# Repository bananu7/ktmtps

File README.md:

# Re-engineering a KTM Throttle Position Sensor

This a repository where I gathered and intend to update all the things related to the KTM 990 TPS. The sensor in those motorcycles is based on a potentiometer, and wears out quickly (head to [Original TPS](/reference/Original.md) for details). As such, I decided to try and create a hall-effect based replacement, as has become the industry standard.

## Work log

### 2024-01-26

It's right past midnight, so it should really be the note for Friday. I got the devkit-v2 casing printed. Quick notes

* needs a chamfer on the bottom where it enters the TBs
* needs more clearance around the pcb perimeter (not much though, likely just pcb has some unevenness)
* needs a bit less clearance for pcb centering tab (the bearing must fit there)
* the shaft needs more clearance inside the bearing (reduce shaft OD)
* bearing into casing clearance is OK
* the cablehole should be oval/wider and can be slightly lower

I'll try to tackle those tomorrow.

### 2024-01-25

The V2 devkits have arrived. Stock photo as they're everywhere:

I'm pleasantly surprised that i got the dimensions almost correctly from the photo. Here's how big the board is:

Since it's a circular shape, it's actually quite easy to design around it. I might just a centering lip to make sure the PCB doesn't rotate, otherwise it'll be held in place by an oring and and a cover.

I have to move the CAD files around, as i started to initially design for my own larger PCB, but the devkit v2 seems to actually be quite good and would save me a lot of time working, ordering and assembling them.

I'm still pondering on whether 2 bearings are even necessary. I might do one of the prototypes with just one bearing and see how it holds up.

### 2024-01-18

I've added early prototype files for CAD and PCB for v2. I think I found a decent way to mount the PCB, utilizing just the outline of the board
with no problematic alignment pins. I'll still need to find a way to do a board cutout to fix the angle, but the oring should keep it in place.
I will also add the screws to the cover and change the shape of the cable route.

I have ordered a couple of smaller devboards, so I might do a v2p CAD version that will accomodate those while i wait/finish my own PCBs.

### 2024-01-16

As almost three years pass from the last update, I decided to go back to the project. The prices of the OEM TPS keep rising, sitting at 160 eur currently. In addition, thanks to @gefr at advrider, we got a confirmation that the 990s ECU will happily work with the AS5600 unit. It's a newer, nicer rotation sensor based on the same principle. It can be trivially programmed via regular SPI without a need for a special programmer, and outputs the desired voltage range as analog PWM directly. So, what seems to remain is making a production-ready prototype.

There are two main challenges that need to be tackled - the PCB and the enclosure; with the latter mostly being dependent on the former. I've ordered a couple of smaller-size development boards from Aliexpress, but I think that eventually I'll need to make a new board. thankfully, the sensor requires absolutely minimum of external components, so the board can be made quite small. I am thinking about making it circular, with a notch for alignment, then covering it with an oring and screwing the cover over.

---

### 2021-09-19

Unfortunately, I got a bit stuck, and with the weather being nice, i just didn't make too much progress. I hope the coming winter months will give me a better time.

The biggest hurdle right now is fixing the dev board in. So far, while I was finally able to print the properly dimensioned pins (using the Cura's "modify mesh settings" to selectively slow down and increase infill for them), the dev board was just made so imprecisely that I couldn't get it to fit nicely. I just need to design my own board and order from JLC again, as that's proven to work way better. I can also include enough space for the mounting screw then.

As far as 3D printing goes, I did some research, and while Nylon (PA12) would be ideal for this application, basing on some tests I found online PLA is actually quite resistant to gasoline! I've mentioned that the ASA parts were disappointing, but I think I'm just going to go with PLA for the first truly functional prototype.

There is an additional thing worth mentioning. While searching the internet, I found a very similarly looking TPS unit, going around for around $20 - supposedly for Polaris vehicles. The physical dimensions look exactly the same, and some tests made on the forum seem to suggest that it might actually be electrically compatible. It has the wrong plug (the opposite sumimoto connector), but that's an easy fix. I've actually ordered one months ago, but Amazon has dropped the ball, so I'm waiting for a package from Aliexpress right now to do my own testing. I am not planning to abandon my project if it turns out to be a drop-in replacement, but it might be a good option for a lot of people.

---

### 2021-07-03

After over two months of waiting, I got a refund for the parts I've ordered and subsequently reordered them. They arrived a few days ago, and I was able to get back on track pretty quickly. This still required some nontrivial operations, though.

First off, in order to speed things up, I've ordered the sensors already soldered on a "development-kit" style of boards. They expose all the pins (7 on the board, because the chip has two Vcc pins, one for 3V3 and one for 5V) and come with convenient passive components. That "convenience" was actually quite problematic, because the way the chip is configured, it doesn't even produce an analog output at all! The R4 resistor puts it in a "programming" mode (the datasheet essentially allows it to be programmed by mechanical placement of the magnet and easy operations even without using I2C at all), so it had to be removed. Similarly, the R1 0Ohm resistor bridges the Vcc pins for 3V3 operation, and the chip works just fine at 5V after I got rid of it. I didn't have to reverse-engineer the board, so thanks to that one random Russian Aliexpress customer that put all of that information in his review.

The board has convenient 4mm mounting holes which I initially assumed to be spaced by 15mm. I took my ready CAD file, got rid of the perimeter plastic around the board (the new one wouldn't fit, anyway) and moved the pins around. That has proven to be an utter failure. Removing the wall around the pins meant that they had much less time to cool on every layer, so they came out as poorly defined blobs that broke out even before I got the print off the bed. No worries, though, as the board didn't fit anyway, with the holes apparently being spaced 16mm in one direction and **15.5mm** in the other. Eek. I just used wood screws to hold the board in place, for now. In fact, those sensors are so good that even holding the magnet in your fingers above the surface produces reasonable results! Compared to my earlier attempts with linear hall sensors, this is a huge difference.

As far as screws go, I was able to find a reasonable mounting screw for now, but I definitely need to redesign the PCB so that it's shorter on one end, because it does get annoying. Having more clearance near the screw would be really helpful.

That being said, after hooking up the direction pin to Vcc (this is a huge benefit of using the 5600 over the 5043!) for counter-clockwise-positive operation and putting it on the TB set, it worked just fine - albeit ratiometrically over 360 degrees. That was already great, though, as the chip can be straightforwardly programmed over just I2C with no HV required. In fact, instead of writing my own library, I used this [excellent example][11] with a human-friendly interface. Unfortunately during testing, even though I only wanted to play with runtime setting, I must've fat-fingered something and burned the angle settings in. Thankfully, the chip can accept that 3 times, so it wasn't bricked just yet.

> Note: The sensor has two possibilities of range settings that were (and still are) a bit confusing to me. Either you write into the MANG (angle) register to set the range of operation, or you write to ZPOS/MPOS to set the start and stop angles (corresponding to 0V and Vcc). Once the ZPOS/MPOS pair has been burned in, the MANG can't even be set dynamically. MANG can be burned in just once. ZPOS/MPOS can be burned in 3 times.

The software in the example works by allowing you to set the start and end values simply by rotating the magnet to appropriate position. Of course this is rather imprecise, but was enough for my testing. One more feature that it has is the raw angle display, which allowed me to more precisely measure the actual operating range of the sensor. To my surprise, it came out to only be **78 degrees**. I am not sure if the TBs have been zeroed-out prior to that, though, and will have to confirm with the original TPS. Either way, that meant that for testing I needed about 140 degrees of 0-5V sweep to get the desired mV/deg to obtain 0.6-3.8V.

This has worked beautifully. I rotated the sensor to indicate almost 0, programmed start position, turned it 140 degrees, programmed end position, and then burned the angle settings and unplugged the I2C connection. This is the first case of a successfully permanently programmed sensor that technically could go into the bike!

#### Wiring

This is also a good point to mention the wiring, as I've been working on that as well. The sensor needs to connect to the bike at the end!

For cables, I've ordered Polish-made TLWY brand ribbons, in 8x0.22mm^2, 8x0.35mm^2 and 8x0.5mm^2 (this corresponds to AWG 24, 22 and 20, respectively). They're of extremely high quality, meeting and exceeding automotive requirements. Even then, I am pretty sure that the original wiring uses AWG 18 cables, but for such a short connection I think I'm going to stick with 20.

The wire thickness is also important for the plug itself. Thanks to some research I found out that the original plugs used by KTM were originally manufactured by Sumimoto (**MT090**, 3-pin). KTM sells them, but they're about half as expensive when bought as generic automotive parts. I was very happy with my cost savings until I've realized that AliExpress has them for 1/5th the price again. Oh well, at least I'll be able to compare them.

To be quite honest, when they arrived, the only main difference seem to be the sealing rubbers. They're much firmer in the original ones, and a bit softer in the Chinese ones. I don't think this will have a huge effect. I mounted one plug so far using the TLWY wires with 1.7mm outer diameter and they seem to seal quite well. My crimping tool is technically only rated to AWG22, but it did just fine with those plugs. I'll wait until I have the casing for the dev-board prototype and will solder them on there.

I also bought a couple of the counterparts to potentially make some test setups. I think that I'll also make a usual Y-splitter to mount on the bike (just like the ones routinely used for TPS setting, even though you'd technically only need to branch that one voltage out).

#### Next steps

This was a long update written over a couple commits, but it represents a significant milestone for me. I've reached the point where I could conceivably take my sensor and plug it into a live bike, and thus its ECU, and see whether it likes the signal or not! I've realized that I don't even have to turn the engine on for that test, I can just ask TuneECU to tell me whether the computer sees the right input.

Before that happens, though, I need to create a proper casing just for the dev-board now and see how my plastic reacts to fuel vapors. I've been also thinking about putting some insulation sheet between the hole where the bearings sit and the electronics, as there need not be a direct contact there. The manual talks about an "airgap", but a thin mylar, kapton or similar sheet should work just fine.

After the unit is enclosed, has a proper screw and the plug connected, I'll consider it the first prototype ready for functional testing. There's a chance I might conduct just the electrical test first, but I see no reason why it shouldn't work with the ECU (since it presents an analog voltage just like a potentiometer would).

Of course even if the prototype works, there's still a question of a new PCB for the AS5600 (with more clearance), the spring loading (I've actually had a simpler idea that would clamp the shaft on the TB arm instead) et cetera, but there might be some things that only the functional testing of the prototype will reveal. I'd put it in my personal motorcycle if not for the fact that it needs to be ready for a long trip soon, so that'll have to wait until then.

---

### 2021-06-14

I've ordered the new sensor from Aliexpress, but the package hasn't arrived yet. In the meantime, I've built an enclosure for my 3D printer and successfully printed some ASA parts. Unfortunately, despite having excellent temperature and UV (we'll see about fuel vapors) resistance, they're much weaker mechanically, which was a disappointment.

---

### 2021-03-28

_This update has been copied from advrider forums._

I have some news - some bad, some good, but worth an update nonetheless.

The video from 2021-03-22 was showing the sensor programmed non-permanently. It had the configuration I needed, but once I resetted it (or cut power) it would go back to stock settings. The special programmer I tried to build was supposed to solve that and allow me to make the settings permanent.

I spent a week on it and got it to the point where I was pretty sure it was going to work, confirming the "correct" operation down to microseconds. Then I plugged the sensor in and... well, bricked it. It received some configuration, but decidedly not what I needed.

I still have a few units left, so I might try to fix the issues with this board, but meanwhile I've found yet another sensor (AS5600) that's:

- a newer design
- more accurate (12 vs 10 bits)
- much easier to program (no special programmer at all) - in fact, the rotation direction has a dedicated pin...
- much easier to solder (SOIC-8 vs SSOP-16)
- 6 times cheaper and easier to obtain
- also automotive-use qualified

I can only kick myself for not noticing it earlier. I think it should be a perfect replacement; I'm going to order some and try to work on the new plans. I wanted to make a V2 PCB anyway, to change the shape and make it easier to fit the mounting screw in the casing. The only downside is waiting for the PCBs to be made again, but after the first run I got more confident in being able to get them to work. I'll try ordering some pre-mounted boards with the new sensor as well to see if I can test it in practice even before my own PCBs are ready. Of course this means I'll need to alter the CAD designs too.

I could probably attack the programmer again and try to get it to work, but I think that at this point the time is better spent into preparing the new sensor; if only for the lower cost and much wider availability!

So while this is a bit of a hiccup, and my next iteration will take about a month to a month and a half to get all parts here, I think I've amassed enough experience to make it much closer to the final product.

In the meantime I might finally take a stab at setting up my 3D-printer for high-temperature materials to see if I'll be able to get a casing what would be usable in a real-world scenario.

---

### 2021-03-25

This is actually a summary of a few days of progress. I started working on the permanent OTP programmer for the AS sensor. I've designed a schematic and built it up on a prototype board from DIP parts. My initial idea was to utilize an ATtiny MCU programmed with the specific bit vector, but for the testing I just plugged the Uno into the DIP 8 socket.

This is the early version of the programmer board when I still thought I could get away with just two transistors. Since then I've severly modified the schematic to utilize a proper NPN driver and added caps across transistor base resistors to improve the shut-off time. The image below shows the delay that was caused by what's apparently called "Miller capacitance" or "charge storage", which I learned on [Electronics.se][10].

I also tried to generate pulses of exactly 2us; that turned out to be quite straighforward using the ATmega's Timer capabilities. The code showcasing that use is in `programmer/code/atmega328p_2u_pulse`.

An important realization I had was that the PROG timings aren't actually that crucial; it's the CLK timings that matter. At first I thought that I'll need to drive the HV line with that accuracy, but I can split the problem up. The PROG line needs to be driven consistently and with not too many transients (check) and the CLK line needs to generate exact 2us pulses (check). I think I have all parts of the puzzle now, what's left now is to integrate them together.

I've also just realized that since I connected the transistors to both PWM pins of the tiny pinout, I have none left for driving the CLK clock precisely. Uh. I'll need to figure something out.

---

### 2021-03-22 

I finally soldered a header to programming pins and took a stab at programming the sensors. So far, they seem to perform the best when the sensor is directly facing the magnet (and not through the PCB), which means the default rotation (value 0 for the MSB direction bit) is wrong.

The sensor can be programmed either permanently (via OTP) or just temporarily. The OTP programming starts with a regular "write" cycle, followed by high voltage pulses that permanently burn Zener diodes inside the chip to store the configuration. The serial interface for interacting with the unit is a bit different to the SSI used for digital readout (BTW, I've realized I skipped the digital data out (DO) on the PCB, which probably wasn't a great idea in retrospect). The SSI uses a very weird signal "delayed" by one clock pulse. The maximum frequency is specified as 1MHz. In contrary, programming allows up to 250kHz comparable to Mode 0 SPI, while the actual OTP burn requires very precisely timed pulses.

My first attempts ended with the chip not responding to anything I was sending so far. All the timings for temporary programming only state maximum values, so I tried slowing down, but that didn't seem to help. I crafted completely bogus waveforms and observed them on the logic analyzer, but I only managed to get some reaction where I completely botched the programming (e.g. disconnected the clock cycle).

Then I had a realization; the non-permanent programming showed `CSn` line going down at the end of it. However, in the OTP burn cycle, the CSn doesn't go down until it ends the enire procedure. Maybe I was supposed to keep it high? Tried that, but it didn't work. In frustration, I manually jerked the CSn line and plugged it into ground... _it worked_.

https://www.youtube.com/watch?v=5MJOhFoH9Xk

I was really tired at that point after going at it for a few hours straight, so decided to only do one more test and call it a night; I added a long delay (2s) and a single up pulse on the CSn line (to mirror the jerky pulses caused by my manual operation which I managed to record on the analyzer), and that also seemed to work. So it's something around either waiting a while, or making one extra pulse on the CSn. I'll try figuring out what the next time (as well as looking at other programming bits), but nevertheless, progress!

P.S. The code for that version is in `programmer/code/as5043_prog_soft`.

---

### 2021-02-19

The PCBs and magnets (6x2mm) arrived. I assembled them:

And mounted in the prototype casings, that I'll commit in a second to the v01 folder. Soldering the chips went quite easily, same with passive parts, even though they might not look as great. Because of limited availability of the passive parts, I decided to go with a voltage divider with 17k4 and 24k3 resistors, giving me slightly too low gain (2.4 vs 2.56 necessary for 90 degrees); that being said, the test was an astounding success, with everything clicking in place just fine, and the sensor immediately reporting stable, predictable readings.

My first idea was to mount the board "chip side up", but the thickness and material of the board in between the magnet and the sensor caused it to have bad, intermittent readings. Flipping the board 180 degrees solved that issue completely. I'll need to add some minor spaces to leave a tiny airgap, because when the magnet touches the chip it's a bit too strong, but otherwise it seems to work fine.

One downside of that orientation is that I'll need to use One-Time Programming to reverse the reported direction, as by default it goes the wrong way. Looking from the TB side, the shaft turns to the left, and by default, with chip facing the magnet, it's turning to the right that increases the voltage. Thankfully I left programming pins on the PCB, so that should go fine.

Another issue I've encountered was that my prototype casing was hard to desing with a screw hole; given the PCB size and the bearing diameter, there's simply very little space to fit one. The next order of business is rectifying that issue somehow.

I also decided that it's the right time to tackle the issue of the spring. My research shows that I'll need around 80Nmm of peak torque at 90 degrees of rotation (actually a bit more than that, because the original sensor has some space around for calibration). This translates to e.g. 1mm thick stainless steel wire with 5 wraps and an outer diameter of 12mm (inner 10mm). Other configurations are possible, and I'll try to order some wire and do some practical experiments. I think making the holes holding the spring itself shouldn't be _that_ hard, but I also need to consider the assembly process. 

---

### 2021-01-14

I created this repo and gathered all the files. I also filled out all the entries below retroactively, to keep the development history intact. The project moves on, and I'm currently ordering the SMD parts, waiting for the PCBs to be fabricated and starting the CAD work for the v01 3D-printed case that will hold the new round magnet and the new PCB.

---

### 2021-01-10

Since the AS5043 is only available in a SSOP-16 SMD package, I wouldn't be able to use it without some breakout board. I decided to create and order a custom PCB for it, that included resistors necessary for an appropriate voltage mapping, and a breakout for programming the unit. The PCB is in the `PCB` folder.

---

### 2021-01-08

During the research about the AS5043 I found [this experiment][6] led by two guys. They originally planned to create a precise motor controller for a resin 3D-printer. The whole method led me to believe that it's totally doable to build a precise sensor with that chip. I also found some interesting devkits from AMS, utilizing [a simple shaft in a piece of acrylic][8], simply holding the magnet on top of the chip (even without any bearings). Despite the datasheet talking about quite strict positioning tolerances, those seemed to work well enough.

Some additional materials include:
 * [the user manual][7]

---

### 2021-01-04

I learned about the existence of [AS5043][5] and the line of those sensors. I still felt there's a lot to be learned from the linear sensor-based approach, but since I could order a few samples, I've decided to give those a shot. They seemed much more straightforward to set up and were specifically designed for potentiometer replacement / TPS use. The samples arrived very quickly, which prompted me to go with that option for now.

I have ordered special radially-polarized magnets for them, too. There's a [special magnet guide][9], but the ones I got were 6mm ones specially labeled for rotation sensors.

---

### 2021-01-02

I got myself a 3D printer and fabricated some of my CAD drafts. They came out well, and allowed for much better tolerances, which in turn meant much better sensor readings. It was still oversaturated, and required being pulled out of the center of the magnets, which probably didn't help the linearity. Around that time I found the [Infineon TPS Application note][4] as well as [the datasheet for their programmable sensor][3]. I wasn't yet very concerned with the electric signals, as I was quite sure I can get the voltage to my desired range using a couple op-amps.

In fact, I did some early tests with an LM258P that seemed to give good results. The maximum voltage achievable with 5V supply is about 3.8V, so about right what the sensor needs to produce.

---

### 2020-11-16

I switched to a free version of Siemens Solid Edge, which helped in the modelling. I have ordered A1324 sensors and bearings and started doing some testing. Those early tests have shown that the sensor is really sensitive to positioning, and simply holding near the magnet won't work.

At first, I tried to put one magnet in the middle of the shaft, and put the sensor to the side, to simplify the construction. This was a complete failure, with wildly varying readings. 

The next tryout utilized a shaft (I used 8mm woodworking pins) drilled longitudinally, with two magnets glued on the sides like in the reference design. This creates a much more linear magnetic field near the sensor. I would later learn that even stronger alignment of the field might be necessary, described in [this application note][4]. I have also learned that the two magnets I used were much too strong and were oversaturating the sensor.

---

### 2020-09-09 - "official start of the project"

I started with [a forum post on AdvRider.com][1] where I gathered the dimensions of the original unit after mine has failed a second time and created a model in FreeCAD. This model can be found in the `CAD/old-freecad` folder.

One of the biggest inspirations for me was [this post][2] on SimHQ forum, describing creation of custom potentiometers for simulation use, utilizing linear hall-effect sensors from Allegro microsystems.

 [1]: https://advrider.com/f/threads/990-throttle-position-sensor-tps-adjustment-video-how-to.1448666/#post-40815732
 [2]: https://simhq.com/forum/ubbthreads.php/topics/3674791/DIY_Sealed_Minature_Hall_Pots
 [3]: https://www.infineon.com/dgdl/Infineon-TLE4997E2-DataSheet-v02_10-EN.pdf?fileId=db3a30431ce5fb52011d3e4c832a2594
 [4]: https://www.infineon.com/dgdl/TLE499x_AppNote_Throttle_Position_Sensing_v1.0.pdf?fileId=db3a30431ce5fb52011d29cc328a1bd2
 [5]: https://ams.com/as5043
 [6]: https://web.archive.org/web/20160315230856/http://sindri.sebastians-site.de/MagneticRotaryEncoder
 [7]: https://ams.com/documents/20143/36005/AS5043_UG000105_1-00.pdf/bf8c0c98-c7ba-e6d1-0d0d-d9de9658eb91
 [8]: https://ams.com/rmh05-dk-xx
 [9]: https://ams.com/documents/20143/36005/AnglePositionOnAxis_AN000271_2-00.pdf/d3bc1235-a3da-7e15-15bf-624e9ff0c389
 [10]: https://electronics.stackexchange.com/questions/555440/transistor-turns-off-only-after-a-delay
 [11]: https://github.com/Seeed-Studio/Seeed_Arduino_AS5600

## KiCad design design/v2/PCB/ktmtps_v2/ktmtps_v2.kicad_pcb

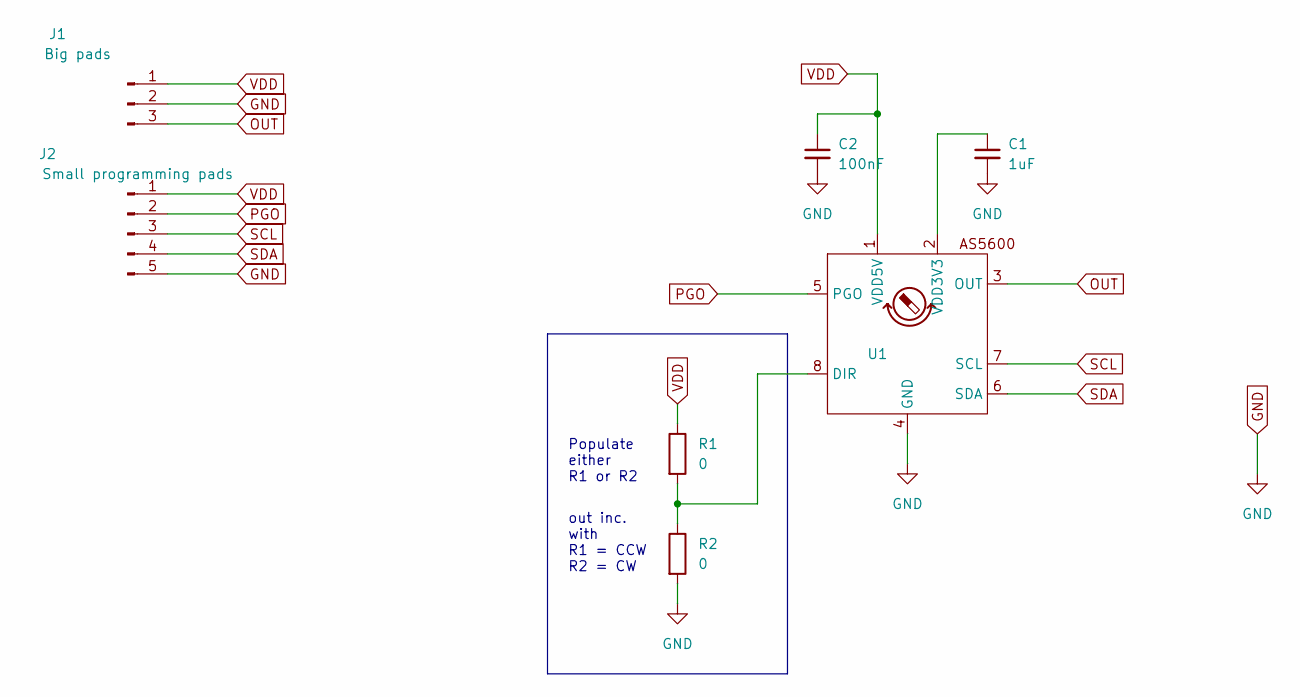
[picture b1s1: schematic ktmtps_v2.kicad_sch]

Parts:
C1: 1uF; C_0805_2012Metric_Pad1.18x1.45mm_HandSolder
C2: 100nF; C_0805_2012Metric_Pad1.18x1.45mm_HandSolder
J1: Big pads; PinHeader_1x03_P1.27mm_Vertical
J2: Small programming pads; SolderWire-0.1sqmm_1x05_P3.6mm_D0.4mm_OD1mm
R1, R2: 0; R_0805_2012Metric_Pad1.20x1.40mm_HandSolder
U1: SOIC-8_3.9x4.9mm_P1.27mm

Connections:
GND: C1.2, C2.2, J1.2, J2.5, R2.2, U1.4 (GND)
unnamed: R1.2, R2.1, U1.8 (DIR)
unnamed: C1.1, U1.2 (VDD3V3)
OUT: J1.3, U1.3 (OUT)
PGO: J2.2, U1.5 (PGO)
SCL: J2.3, U1.7 (SCL)
SDA: J2.4, U1.6 (SDA)
VDD: C2.1, J1.1, J2.1, R1.1, U1.1 (VDD5V)

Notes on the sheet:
Populate either R1 or R2
out inc. with R1 = CCW R2 = CW

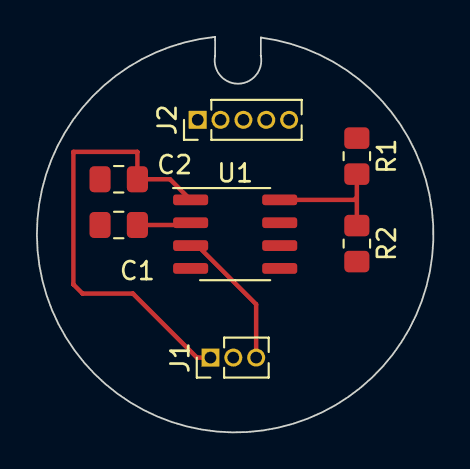
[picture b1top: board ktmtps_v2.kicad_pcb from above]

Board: 2 copper layers, 22.0 x 22.0 mm, 7 parts (0 on the bottom side), 8 nets.

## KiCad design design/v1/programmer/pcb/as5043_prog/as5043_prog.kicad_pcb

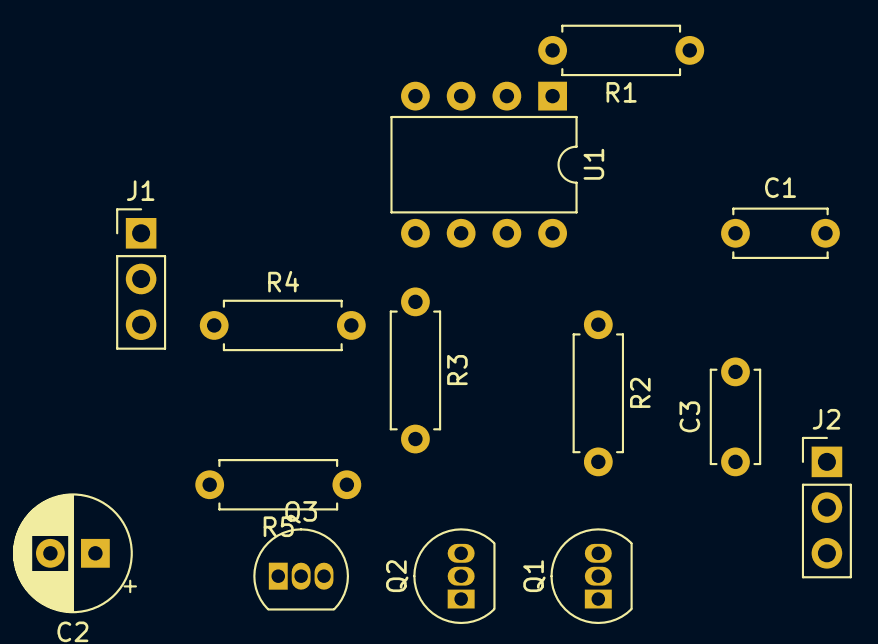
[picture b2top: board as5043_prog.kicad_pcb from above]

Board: 2 copper layers, 14 parts (0 on the bottom side), 13 nets, no tracks yet.

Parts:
C1: 0.1uF; C_Disc_D5.0mm_W2.5mm_P5.00mm
C2: 10uF; CP_Radial_D6.3mm_P2.50mm
C3: 10nF; C_Disc_D5.0mm_W2.5mm_P5.00mm
J1, J2: Conn_01x03_Male; PinHeader_1x03_P2.54mm_Vertical
Q1, Q2: 8550SS; TO-92_Inline
Q3: BC547; TO-92_Inline
R1, R4: 10K; R_Axial_DIN0207_L6.3mm_D2.5mm_P7.62mm_Horizontal
R2, R3, R5: 1K; R_Axial_DIN0207_L6.3mm_D2.5mm_P7.62mm_Horizontal
U1: ATtiny13A-PU; DIP-8_W7.62mm

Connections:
+5V: C1.1, J1.1, Q1.1, R1.1, U1.8
+7.5V: C2.1, J1.2, Q2.1, R4.1
/CLK: J2.2, U1.7
/CSN: J2.3, U1.2
/PROG: C3.1, J2.1, Q1.2, Q2.2
/PROG_HV: R3.1, U1.5
/PROG_LV: R2.1, U1.6
GND: C1.2, C2.2, C3.2, J1.3, Q3.3, U1.4
unnamed: Q1.3, R2.2
unnamed: Q2.3, R5.2
unnamed: Q3.1, R4.2, R5.1
unnamed: Q3.2, R3.2
unnamed: R1.2, U1.1

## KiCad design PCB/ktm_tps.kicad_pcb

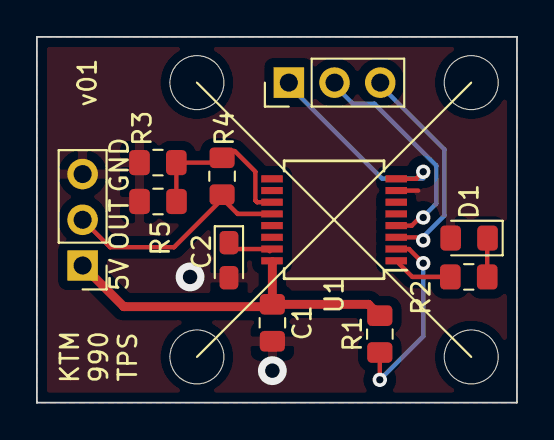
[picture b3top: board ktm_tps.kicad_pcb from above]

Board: 2 copper layers, 26.7 x 20.3 mm, 15 parts (0 on the bottom side), 11 nets.

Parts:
C1: 100n; C_0805_2012Metric_Pad1.15x1.40mm_HandSolder
C2: 1...10uF; CP_EIA-2012-15_AVX-P_Pad1.30x1.05mm_HandSolder
D1: LED; LED_0805_2012Metric_Pad1.15x1.40mm_HandSolder
H1, H2, H3, H4: MountingHole; MountingHole_3mm
J1, J2: Conn_01x03_Male; PinHeader_1x03_P2.54mm_Vertical
R1: 0; R_0805_2012Metric_Pad1.15x1.40mm_HandSolder
R2: 1k; R_0805_2012Metric_Pad1.15x1.40mm_HandSolder
R3: 10k 1%; R_0805_2012Metric_Pad1.15x1.40mm_HandSolder
R4: 2.8k 1%; R_0805_2012Metric_Pad1.15x1.40mm_HandSolder
R5: 0-DNP; R_0805_2012Metric_Pad1.15x1.40mm_HandSolder
U1: AS5043; SSOP-16_5.3x6.2mm_P0.65mm

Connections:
+5V: C1.1, J1.1, R1.1, U1.16
CLK: J2.2, U1.4
CS: J2.3, U1.3
GND: C1.2, C2.2, D1.2, J1.3, R3.1, R5.1, U1.7
unnamed: C2.1, U1.15
unnamed: D1.1, R2.1
unnamed: R1.2, U1.2
unnamed: R2.2, U1.1
unnamed: R3.2, R4.1, R5.2, U1.11
PROG: J2.1, U1.8
TPS_OUT: J1.2, R4.2, U1.12

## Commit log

2021-01-14 Added the v1 of the PCB layout
2021-01-14 Added v1 of the PCB
2021-01-14 Added the original FreeCAD model
2021-01-14 Added the v0 - based on the linear Hall effect sensor with two magnets
2021-01-14 Added some descriptions of the original sensor and retroactive logs
2021-01-14 Added missing part files of v0
2021-01-14 Added some more links from AMS to readme
2021-02-19 Update with new board/new casing/as5043
2021-02-19 Added the model of the throttle body receptacle
2021-02-19 Added v01 casing, shaft and assembly
2021-03-22 Added update about programming
2021-03-26 Added the programmer schematic
2021-03-26 Added a lab note about the programmer and the programmer source tryouts
2021-03-26 Fixed the readme links
2021-03-26 Added programmer image
2021-03-26 Added date to 25th march post
2021-06-15 Added some small changes to the programmer electronics
2021-06-15 Added gitignore and some info to docs
2021-06-15 Added some updated CAD files
2021-06-15 Added gitignore to programmer folder
2021-06-15 Added exported BOM for the PCB for some reason
2021-07-03 Added some more notes, programmer 2 pic etc
2021-07-03 Started working on july update
2021-07-03 Added wiring notes and mostly finished july note
2021-07-03 Added more into the July update about the operation and next steps
2021-09-19 Update README.md
    Added OSHW logo, fixed missing link, fixed typo
2021-09-19 Added a september note
    Added OSHW logo, fixed missing link, fixed typo
2021-09-19 Create LICENSE
2024-01-18 Reorg
2024-01-18 Added log entr
2024-01-18 Added early version of v2
2024-01-18 Added log
2024-01-18 Added some crap to gitignore
2024-01-18 Moved the v2 base to componentsg
2024-01-25 Some more work on the v2
2024-01-26 Log 2023-01-27

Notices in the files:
PCB/ktm_tps.kicad_pcb:
Licence: CC BY 4.0
CC-BY 4.0
creativecommons.org
